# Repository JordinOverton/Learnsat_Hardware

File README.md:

# LearnSAT Hardware GitHub Repository

## All files related to the OBC, Boba, and PoBoI are located in their respective folders

## Please ensure all commits have MEANINGFUL descriptions behind what has been changed

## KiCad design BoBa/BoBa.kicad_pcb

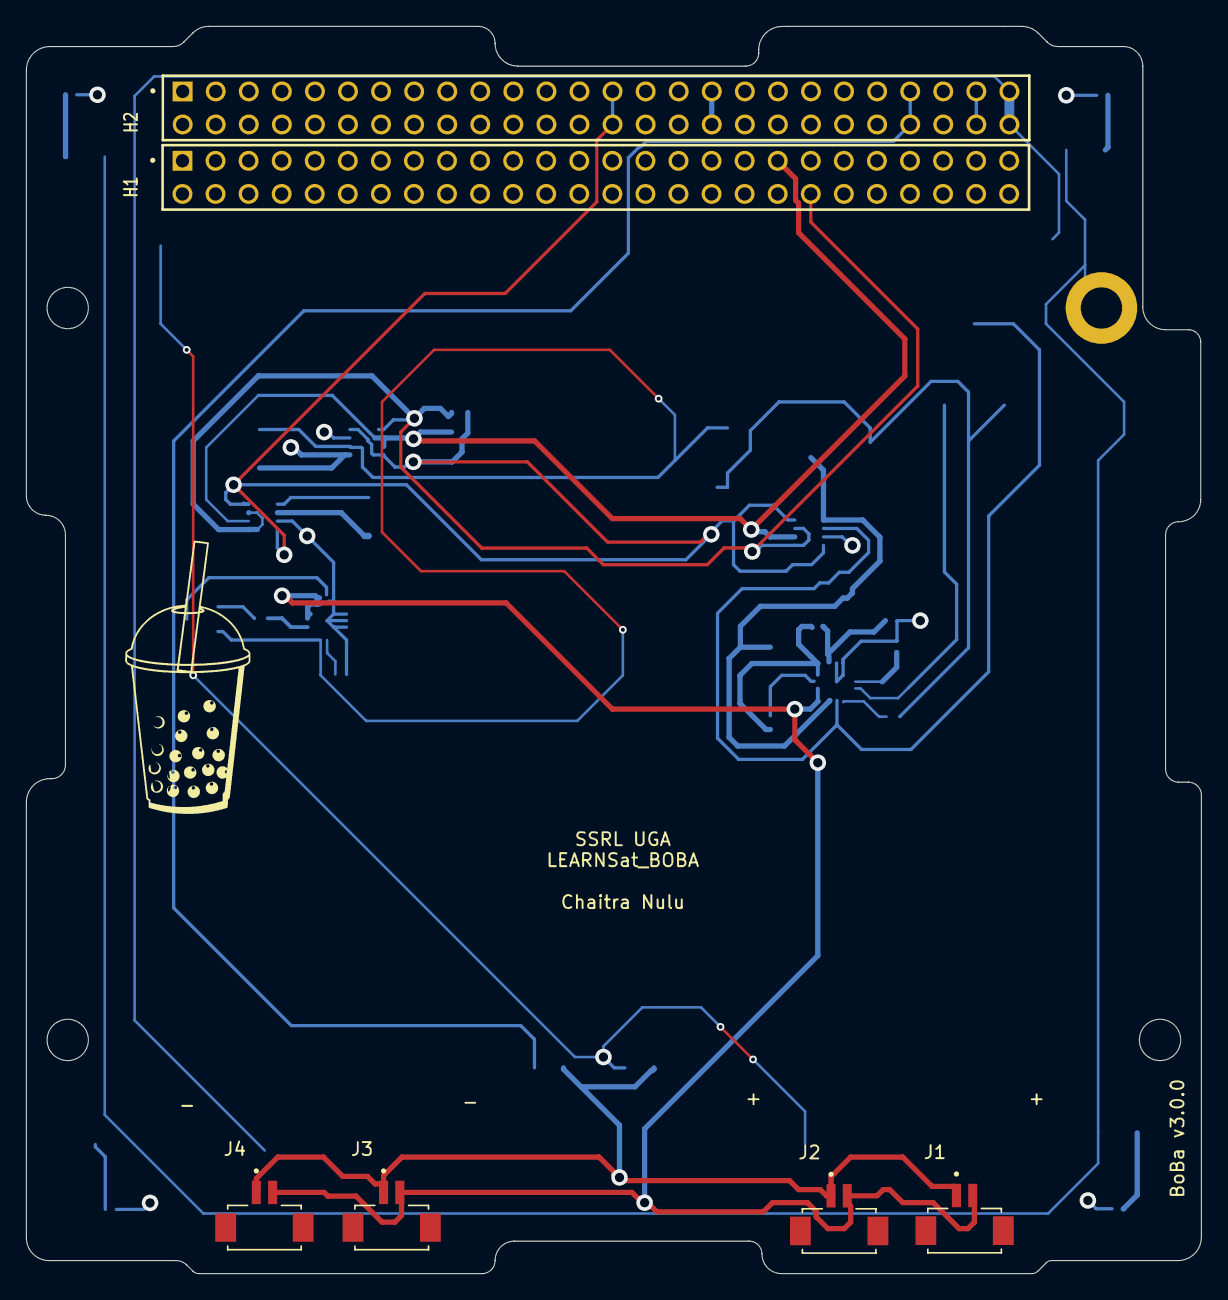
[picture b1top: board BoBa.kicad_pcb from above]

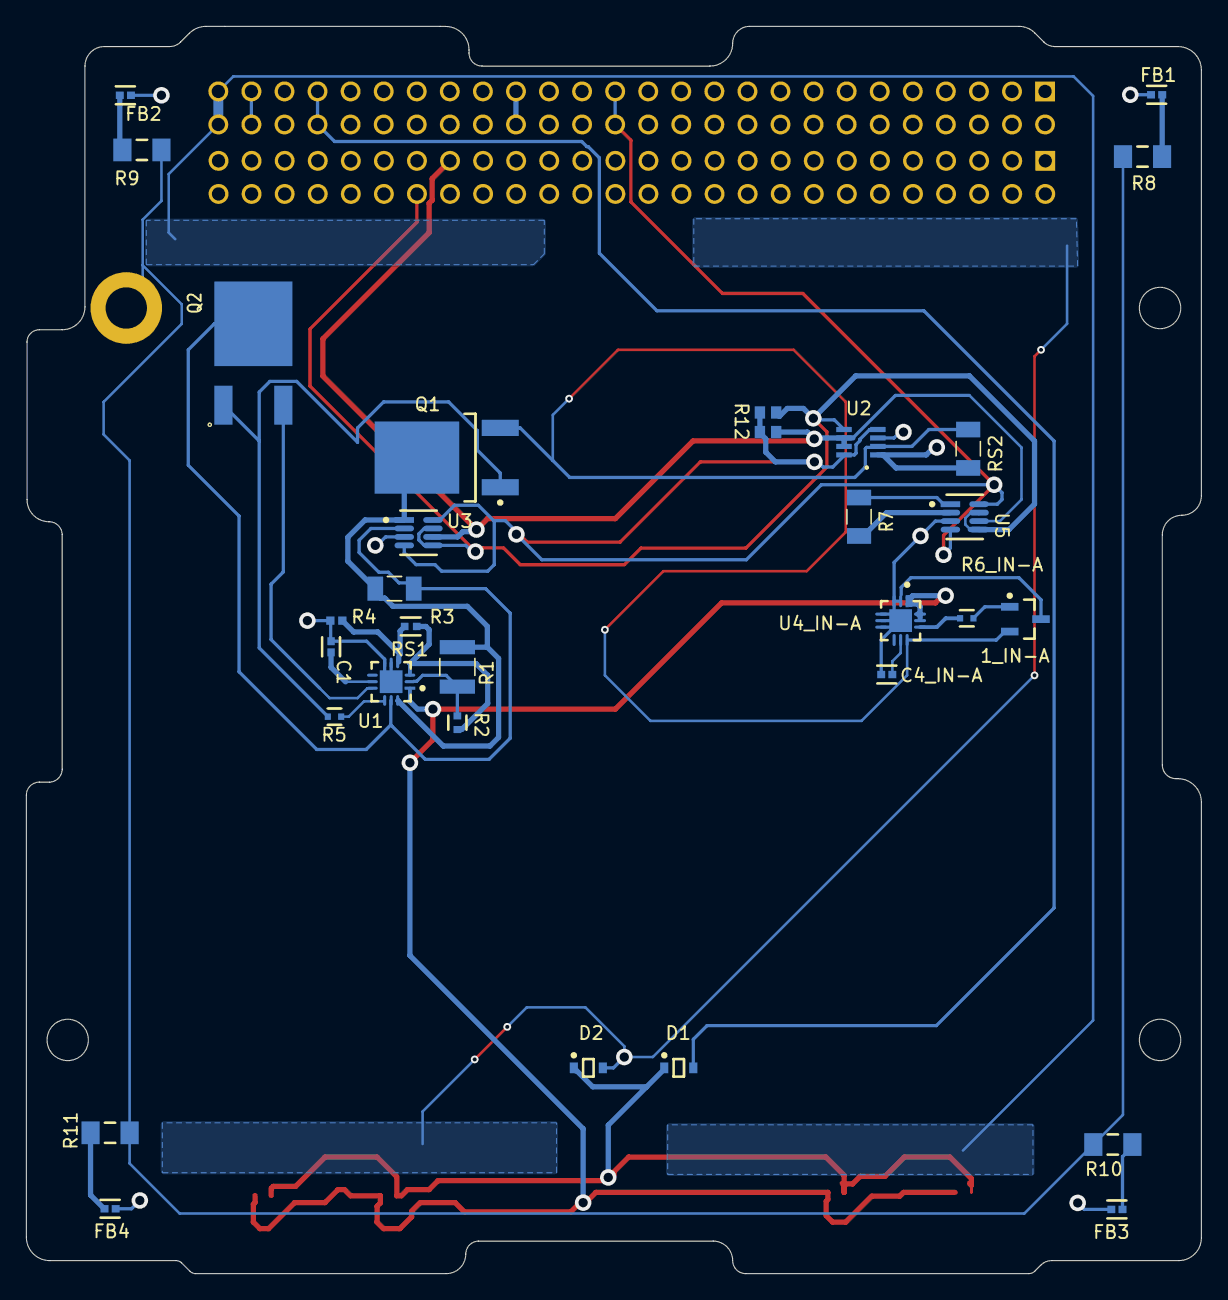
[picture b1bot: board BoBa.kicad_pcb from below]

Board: 4 copper layers, 90.3 x 95.8 mm, 37 parts (31 on the bottom side), 31 nets.

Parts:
1_IN-A: 2N7002; INF-PG-SOT23_M
  : CRCW06034K70FKTA; RESC1609X50X30NL10T20
C1, C4_IN-A: GRM155R71H472KA01D; FP-GRM155-0_05-IPC_B
D1, D2: BAT54HT1G; ONSC-SOD-323-2-477-02_V
FB1, FB2, FB3, FB4: BLM15AG102SN1D; FP-BLM15-0_05-IPC_B
H1, H2: SSQ-126-X-G-D; SAMTEC_SSQ-126-X-G-D
J1, J2, J3, J4: DF13C-2P-1.25V(21); HRS_DF13C-2P-1.25V(21)
Q1: FQD13N06LTM; FAIR-TO-252-3_V
Q2: FQD13N06LTM; TO229P991X239-3N
R1: CRCW1210900RFKTA; RESC3225X60N
R2: RG1005N-202-B-T5; FP-RG1005-MFG
R3: RG1005N-183-W-T5; FP-RG1005-IPC_B
R4: 96kOhm Resistor; CAPC1005X06N
R5, R6_IN-A: ERJ-2RKF10R0X; FP-ERJ2RK-MFG
R7: PE1206DRM470R025L1; RESC3216X89N
R8, R9, R10, R11: Resistor 1k +/-1% 1206 250 mW; RESC3116X70X50ML13T20
R12: CRCW06034K70FKTA; RESC1609X50X30NL10T20
RS1, RS2: PE1206DRM470R025L; RESC3216X89N
U1: LTC4231HUD-2#TRPBF; FP-UD-12-05-08-1855-IPC_B
U2: INA219; SOT23-8
U3, U5: INA219AIDCNR; FP-DCN0008A-IPC_B
U4_IN-A: LTC4231IUD-2#TRPBF; FP-UD-12-05-08-1855-IPC_A

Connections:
3V3_Secondary: .1, H2.27, H2.28, R12.1, U2.4, U2.8, U3.4, U3.8, U5.4, U5.8
3v3_Primary: H2.33, H2.34
Chassis GND: R8.2, R9.2, R10.2, R11.2
GND: 1_IN-A.3, C1.2, C4_IN-A.2, FB1.1, FB2.1, FB3.1, FB4.1, H2.13, H2.14, H2.29, H2.30, H2.31, H2.32, R4.2, U1.5, U1.6, U1.13, U2.3, U3.3, U4_IN-A.2, U4_IN-A.3, U4_IN-A.4, U4_IN-A.5, U4_IN-A.6, U4_IN-A.13, U5.3
G_IN-G: 1_IN-A.1, R6_IN-A.1
I2C Clock: .2, H1.40, U2.5, U3.5, U3.7, U5.5, U5.7
I2C Data: H1.37, R12.2, U2.6, U2.7, U3.6, U5.6
INHIBIT: J1.2, J2.2, J3.2, J4.2, U1.1, U4_IN-A.1, U4_IN-A.11, U4_IN-A.12
NetC1_1: C1.1, U1.8
NetC4_IN-G_1: C4_IN-A.1, U4_IN-A.8
NetD1_1: D1.1, D2.1, J1.1, J2.1, J3.1, J4.1
NetFB1_2: FB1.2, R8.1
NetFB2_2: FB2.2, R9.1
NetFB3_2: FB3.2, R10.1
NetFB4_2: FB4.2, R11.1
NetQ1_4: Q1.4, R1.2, RS1.1, U1.12, U3.1
NetQ2_1: Q1.1, Q2.1, R5.1
NetQ2_3: Q2.3, U1.9
NetQ2_4: Q2.4, RS1.2, U1.11, U3.2
NetR1_1: R1.1, R2.1, U1.2
NetR2_2: R2.2, R3.1, U1.3
NetR3_2: R3.2, R4.1, U1.4
NetR5_2: R5.2, U1.10
NetR6_IN-G_2: R6_IN-A.2, U4_IN-A.10
NetR7_1: R7.1, U5.2
NetR7_2: R7.2, U5.1
Pack+_Neg: H2.51, H2.52
Pack+_Pos: D2.2, RS2.1, U2.1
Pack-_Neg: 1_IN-A.2, Q1.3, RS2.2, U2.2, U4_IN-A.9
VBatt: H2.49, H2.50
Vmppt: D1.2, H2.45, H2.46

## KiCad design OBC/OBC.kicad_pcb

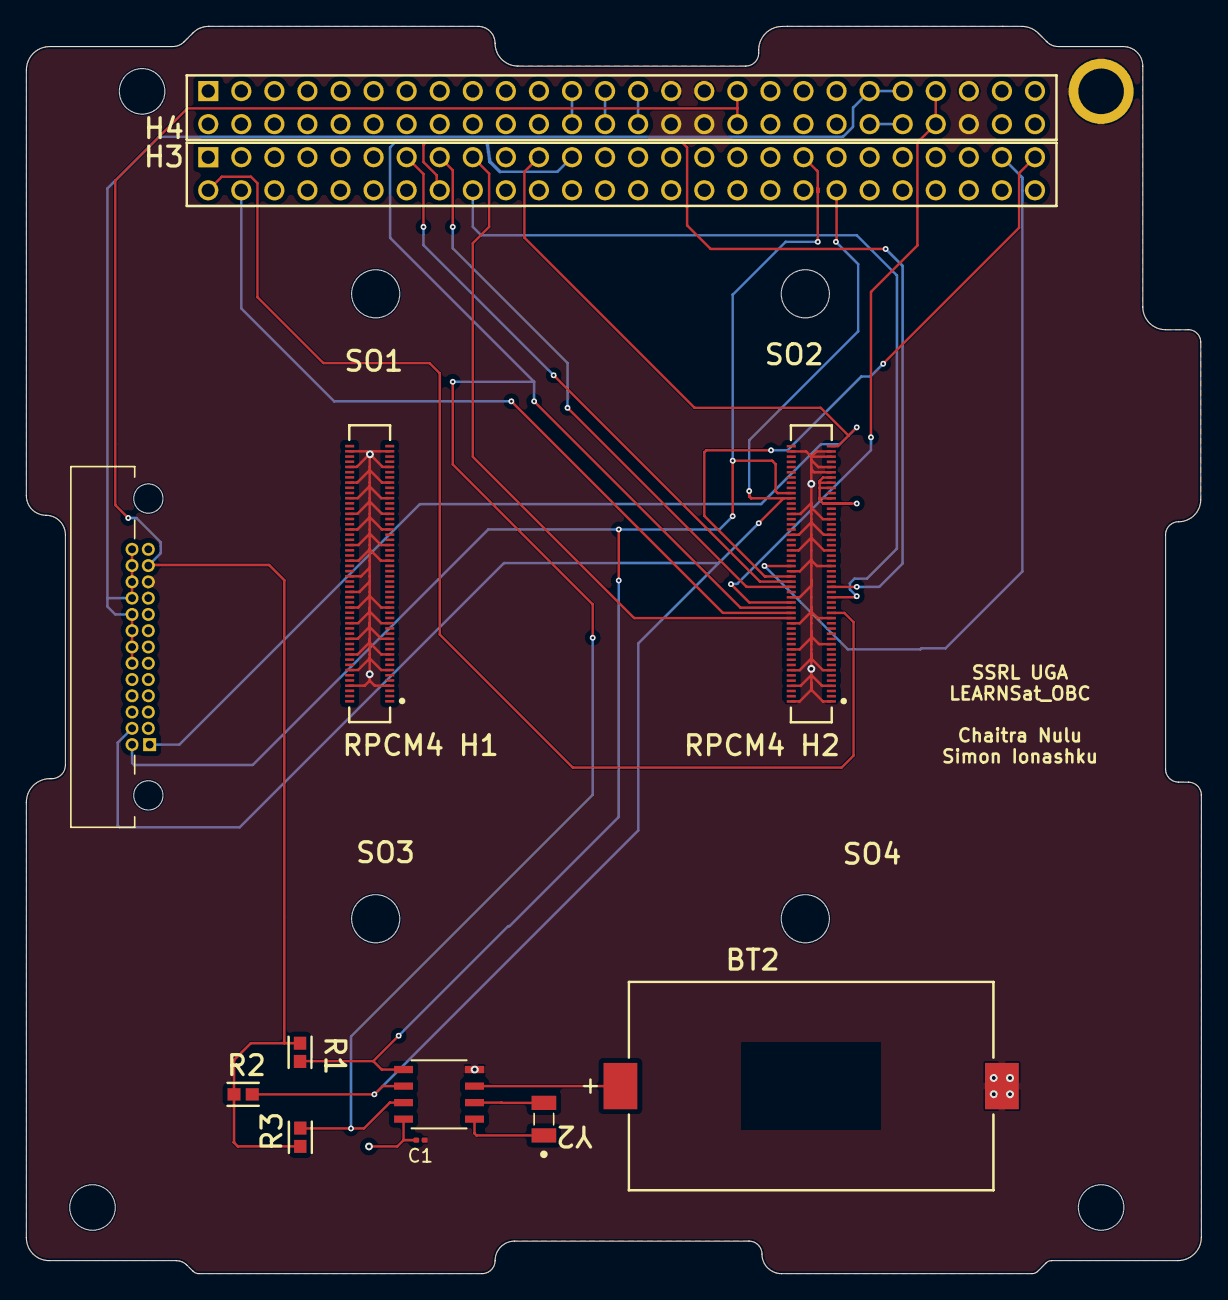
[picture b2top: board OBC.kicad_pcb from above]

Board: 4 copper layers, 90.3 x 95.8 mm, 10 parts (0 on the bottom side), 21 nets.

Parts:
BT2: BA2032SM; MPD-BA2032SM_V
C1: 100nf; C_0201_0603Metric
H3, H4: SSQ-126-22-G-D; SMTC-SSQ-126-22-X-D
R1, R2, R3: Comment; FP-RMCF0603-IPC_B
RPCM4 H1, RPCM4 H2: Comment; FP-DF40HC_3_0_-100DS-0_4V-MFG
Y2: ECS-.327-12.5-34RR-TR; XTAL_ECS-.327-12.5-34RR-TR

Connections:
3V3_Primary: H4.33, H4.34, R1.1, R2.1, R3.1
3V3_Secondary: H4.27, H4.28
5V_Primary: C1.1, H4.23, H4.24, RPCM4 H2.77, RPCM4 H2.79, RPCM4 H2.83, RPCM4 H2.85, RPCM4 H2.87
5V_Secondary: H4.25, H4.26
GND: BT2.2, C1.2, H4.29, H4.30, H4.31, H4.32, H4.47, H4.48, RPCM4 H1.7, RPCM4 H1.8, RPCM4 H1.13, RPCM4 H1.14, RPCM4 H1.19, RPCM4 H1.20, RPCM4 H1.25, RPCM4 H1.26, RPCM4 H1.31, RPCM4 H1.32, RPCM4 H1.37, RPCM4 H1.38, RPCM4 H1.44, RPCM4 H1.50, RPCM4 H1.55, RPCM4 H1.56, RPCM4 H1.61, RPCM4 H1.62, RPCM4 H1.67, RPCM4 H1.68, RPCM4 H1.73, RPCM4 H1.74, RPCM4 H1.79, RPCM4 H1.80, RPCM4 H1.85, RPCM4 H1.86, RPCM4 H1.91, RPCM4 H1.92, RPCM4 H1.97, RPCM4 H1.98, RPCM4 H2.1, RPCM4 H2.2, RPCM4 H2.7, RPCM4 H2.8, RPCM4 H2.13, RPCM4 H2.14, RPCM4 H2.22, RPCM4 H2.23, RPCM4 H2.32, RPCM4 H2.33, RPCM4 H2.42, RPCM4 H2.52, RPCM4 H2.53, RPCM4 H2.59, RPCM4 H2.60, RPCM4 H2.65, RPCM4 H2.66, RPCM4 H2.71, RPCM4 H2.74, RPCM4 H2.89, RPCM4 H2.91, RPCM4 H2.95, RPCM4 H2.97, RPCM4 H2.98
GPIO 4: H3.49, RPCM4 H2.54
GPIO 5: H3.17, RPCM4 H2.34
GPIO 17: H3.51, RPCM4 H2.50
GPIO 22: H3.15, RPCM4 H2.46
GPIO 24: H3.16, RPCM4 H2.45
GPIO 25: H3.18, RPCM4 H2.41
GPIO 27: H3.13, RPCM4 H2.48
OBC_HB: H3.23, R3.2, RPCM4 H2.38
OBC_RST: H3.21, RPCM4 H2.99
SCL: H3.40, R2.2, RPCM4 H2.80
SDA: H3.37, R1.2, RPCM4 H2.82
UART_RX: H3.4, RPCM4 H2.36
UART_TX: H3.2, RPCM4 H2.35
VBATT_Primary: H4.41, H4.43
VBATT_Secondary: H4.42, H4.44
Vmppt: H4.45, H4.46, RPCM4 H2.40
